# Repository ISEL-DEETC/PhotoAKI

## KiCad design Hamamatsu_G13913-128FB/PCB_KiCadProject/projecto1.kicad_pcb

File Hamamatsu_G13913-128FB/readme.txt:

This folder contains all the project files related to the multichannel optical detector
based on Hamamatsu's G13913-128FB linear image sensor.

Folder STM32_ImageSensor contains the Arduino project files for the STM32 microcontroller. 
Instructions on how to install the required packages and drivers to use STM32 MCU with
tne Arduino IDE are included in the main project file.

Folder PCB_KiCadProject contains the project files for the PCB in which the image sensor 
is mounted and connected to the MCU development board. The gerber files used to
manufacture the first prototype through JLCPCB's services are also included.

Folder ArduinoDue_TestSignals contains the Arduino project file for an ArduinoDue board
to generate test signals for the detection system.

Folder PhotonicImagingApp_Installer contains the installation files for the Windows
Application to control the detection module. The source files for the application
are archived in the VisualStudio_PhotonicImagingAppProject.zip file.

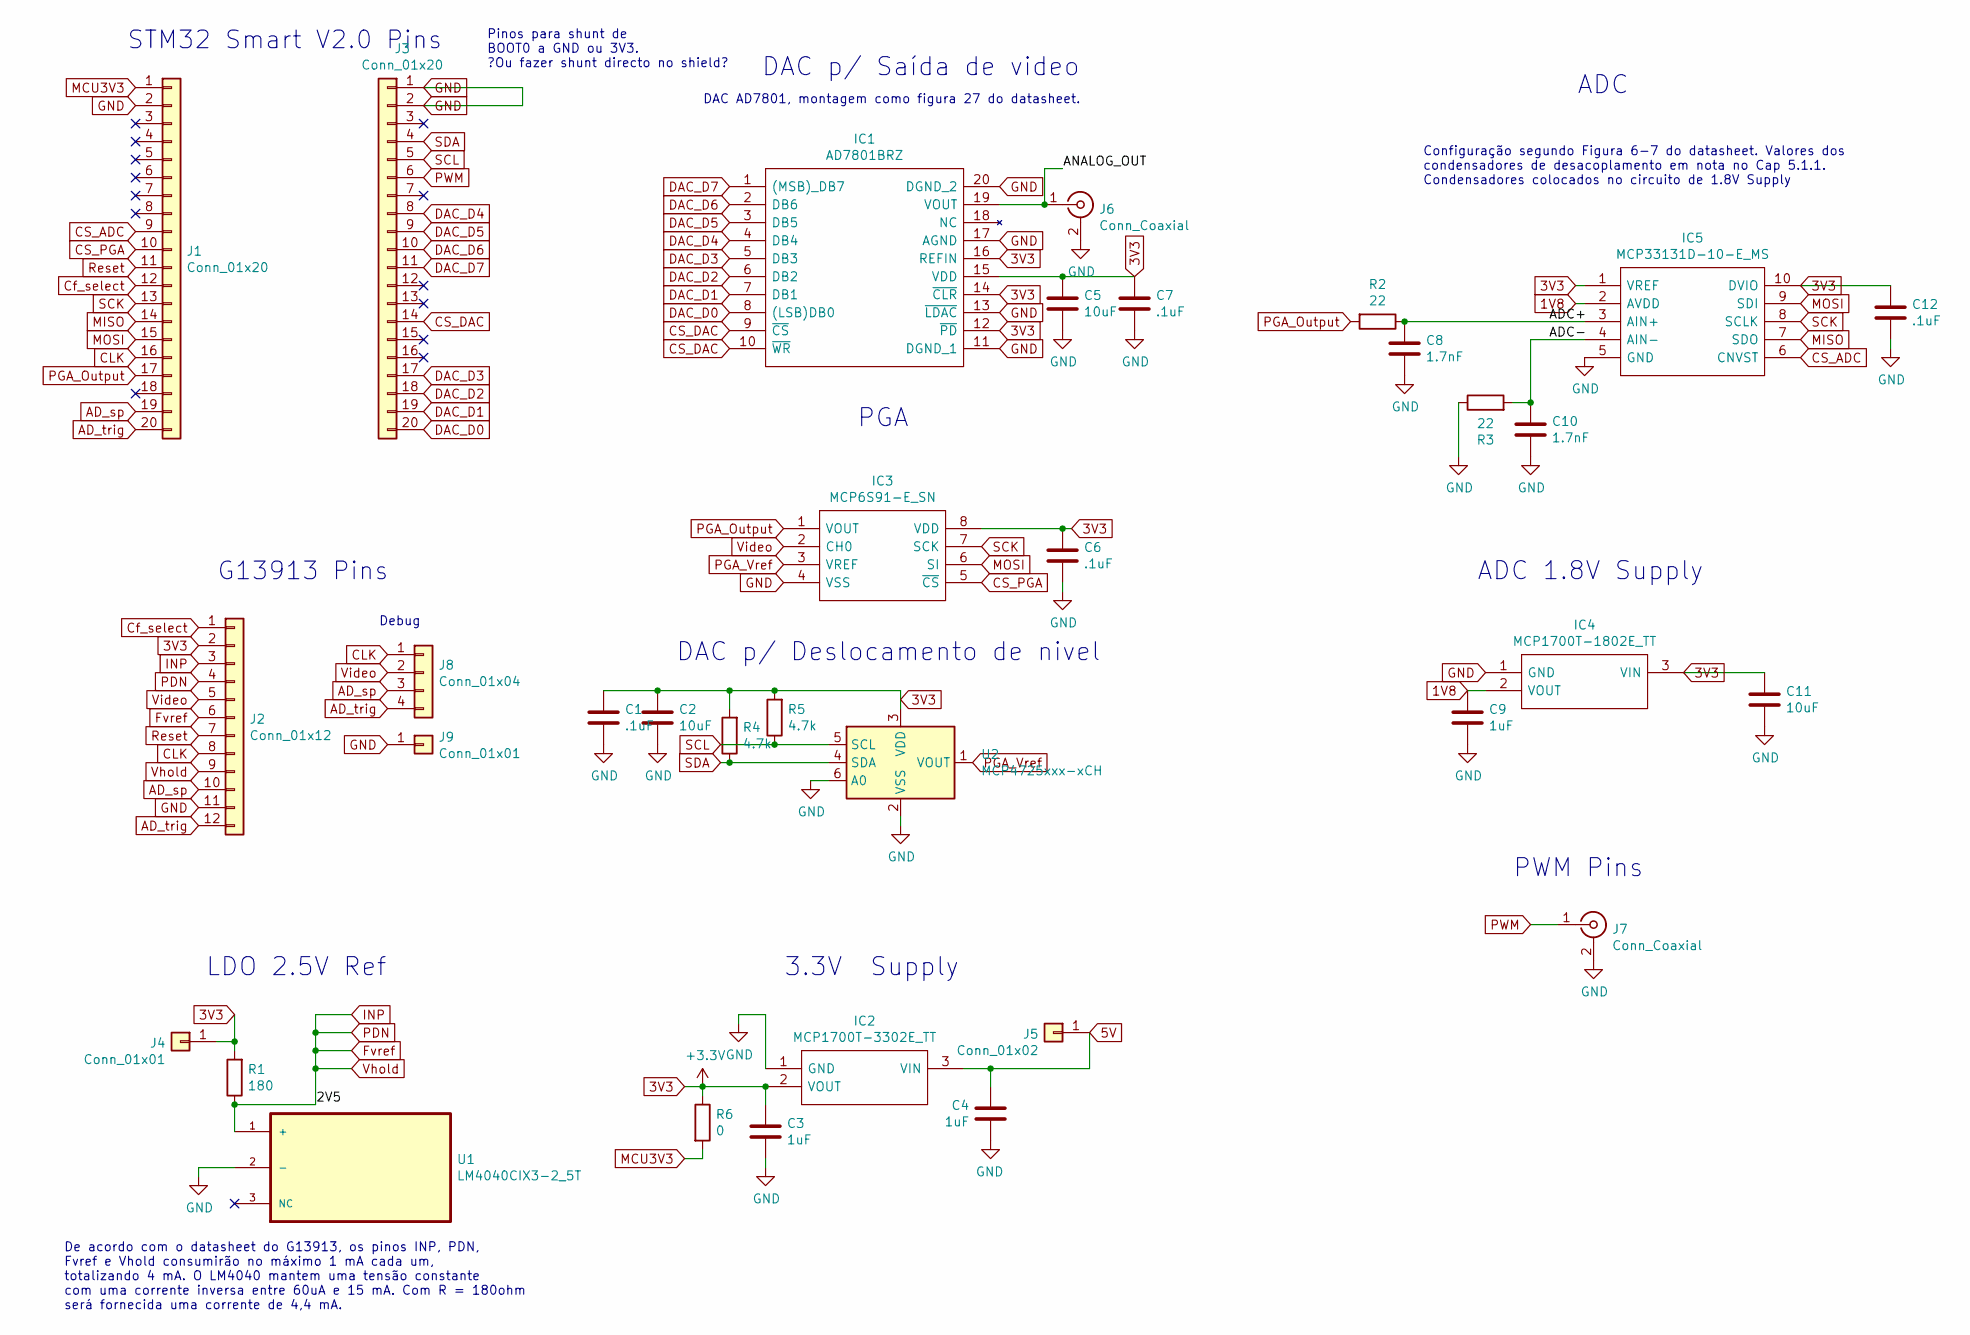
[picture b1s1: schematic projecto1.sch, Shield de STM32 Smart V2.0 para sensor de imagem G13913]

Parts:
C1, C6, C7, C12: .1uF; C_1206_3216Metric_Pad1.33x1.80mm_HandSolder
C2, C5, C11: 10uF; C_1206_3216Metric_Pad1.33x1.80mm_HandSolder
C3, C4, C9: 1uF; C_1206_3216Metric_Pad1.33x1.80mm_HandSolder
C8, C10: 1.7nF; C_1206_3216Metric_Pad1.33x1.80mm_HandSolder
IC1: AD7801BRZ; SOIC127P1032X265-20N; Manufacturer_Part_Number AD7801BRZ; Mouser Part Number 584-AD7801BRZ
IC2: MCP1700T-3302E_TT; SOT95P237X112-3N; Mouser Part Number 579-MCP1700T3302E/TT
IC3: MCP6S91-E_SN; SOIC127P600X175-8N; Manufacturer_Part_Number MCP6S91-E/SN; Mouser Part Number 579-MCP6S91-E/SN
IC4: MCP1700T-1802E_TT; SOT95P237X112-3N; Manufacturer_Part_Number MCP1700T-1802E/TT; Mouser Part Number 579-MCP1700T1802E/TT
IC5: MCP33131D-10-E_MS; SOP50P490X110-10N; Mouser Part Number 579-MCP33131D10EMS
J1, J3: Conn_01x20; PinHeader_1x20_P2.54mm_Vertical
J2: Conn_01x12; Hirose_FH12-12S-0.5SH_1x12-1MP_P0.50mm_Horizontal
J4, J9: Conn_01x01; PinHeader_1x01_P2.54mm_Vertical
J5: Conn_01x02; PinHeader_1x01_P2.54mm_Vertical
J6, J7: Conn_Coaxial; PCBSMAFRAHT
J8: Conn_01x04; PinHeader_1x04_P2.54mm_Vertical
R1: 180; R_1206_3216Metric_Pad1.30x1.75mm_HandSolder
R2, R3: 22; R_1206_3216Metric_Pad1.30x1.75mm_HandSolder
R4, R5: 4.7k; R_1206_3216Metric_Pad1.30x1.75mm_HandSolder
R6: 0; R_0805_2012Metric_Pad1.20x1.40mm_HandSolder
U1: LM4040CIX3-2_5T; SOT65P210X110-3N
U2: MCP4725xxx-xCH; SOT-23-6

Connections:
1V8: C9.1, IC4.2 (VOUT), IC5.2 (AVDD)
3V3: C1.1, C2.1, C3.1, C5.1, C6.1, C7.1, C11.1, C12.1, IC1.12 (~PD), IC1.14 (~CLR), IC1.15 (VDD), IC1.16 (REFIN), IC2.2 (VOUT), IC3.8 (VDD), IC4.3 (VIN), IC5.1 (VREF), IC5.10 (DVIO), J2.2, J4.1, R1.2, R4.2, R5.2, R6.1, U2.3 (VDD)
5V: C4.1, IC2.3 (VIN), J5.1
/ADC+: C8.1, IC5.3 (AIN+), R2.1
/ADC-: C10.1, IC5.4 (AIN-), R3.2
/ANALOG_OUT: IC1.19 (VOUT), J6.1 (In)
AD_sp: J1.19, J2.10, J8.3
AD_trig: J1.20, J2.12, J8.4
CLK: J1.16, J2.8, J8.1
CS_ADC: IC5.6 (CNVST), J1.9
CS_DAC: IC1.9 (~CS), IC1.10 (~WR), J3.14
CS_PGA: IC3.5 (~CS), J1.10
Cf_select: J1.12, J2.1
DAC_D0: IC1.8 ((LSB)DB0), J3.20
DAC_D1: IC1.7 (DB1), J3.19
DAC_D2: IC1.6 (DB2), J3.18
DAC_D3: IC1.5 (DB3), J3.17
DAC_D4: IC1.4 (DB4), J3.8
DAC_D5: IC1.3 (DB5), J3.9
DAC_D6: IC1.2 (DB6), J3.10
DAC_D7: IC1.1 ((MSB)_DB7), J3.11
Fvref: J2.3, J2.4, J2.6, J2.9, R1.1, U1.1 (+)
GND: C1.2, C2.2, C3.2, C4.2, C5.2, C6.2, C7.2, C8.2, C9.2, C10.2, C11.2, C12.2, IC1.11 (DGND_1), IC1.13 (~LDAC), IC1.17 (AGND), IC1.20 (DGND_2), IC2.1 (GND), IC3.4 (VSS), IC4.1 (GND), IC5.5 (GND), J1.2, J2.11, J3.1, J3.2, J6.2 (Ext), J6.4, J7.2 (Ext), J7.4, J9.1, R3.1, U1.2 (-), U2.2 (VSS), U2.6 (A0)
MCU3V3: J1.1, R6.2
MISO: IC5.7 (SDO), J1.14
MOSI: IC3.6 (SI), IC5.9 (SDI), J1.15
PGA_Output: IC3.1 (VOUT), J1.17, R2.2
PGA_Vref: IC3.3 (VREF), U2.1 (VOUT)
PWM: J3.6, J7.1 (In)
Reset: J1.11, J2.7
SCK: IC3.7 (SCK), IC5.8 (SCLK), J1.13
SCL: J3.5, R5.1, U2.5 (SCL)
SDA: J3.4, R4.1, U2.4 (SDA)
Video: IC3.2 (CH0), J2.5, J8.2

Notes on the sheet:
STM32 Smart V2.0 Pins
G13913 Pins
ADC 1.8V Supply
LDO 2.5V Ref
3.3V Supply
DAC p/ Saída de video
ADC
PGA
Configuração segundo Figura 6-7 do datasheet. Valores dos condensadores de desacoplamento em nota no Cap 5.1.1. Condensadores colocados no circuito de 1.8V Supply
DAC AD7801, montagem como figura 27 do datasheet.
Pinos para shunt de BOOT0 a GND ou 3V3. ?Ou fazer shunt directo no shield?
DAC p/ Deslocamento de nivel
PWM Pins
De acordo com o datasheet do G13913, os pinos INP, PDN, Fvref e Vhold consumirão no máximo 1 mA cada um, totalizando 4 mA. O LM4040 mantem uma tensão constante com uma corrente inversa entre 60uA e 15 mA. Com R = 180ohm será fornecida uma corrente de 4,4 mA.
Debug

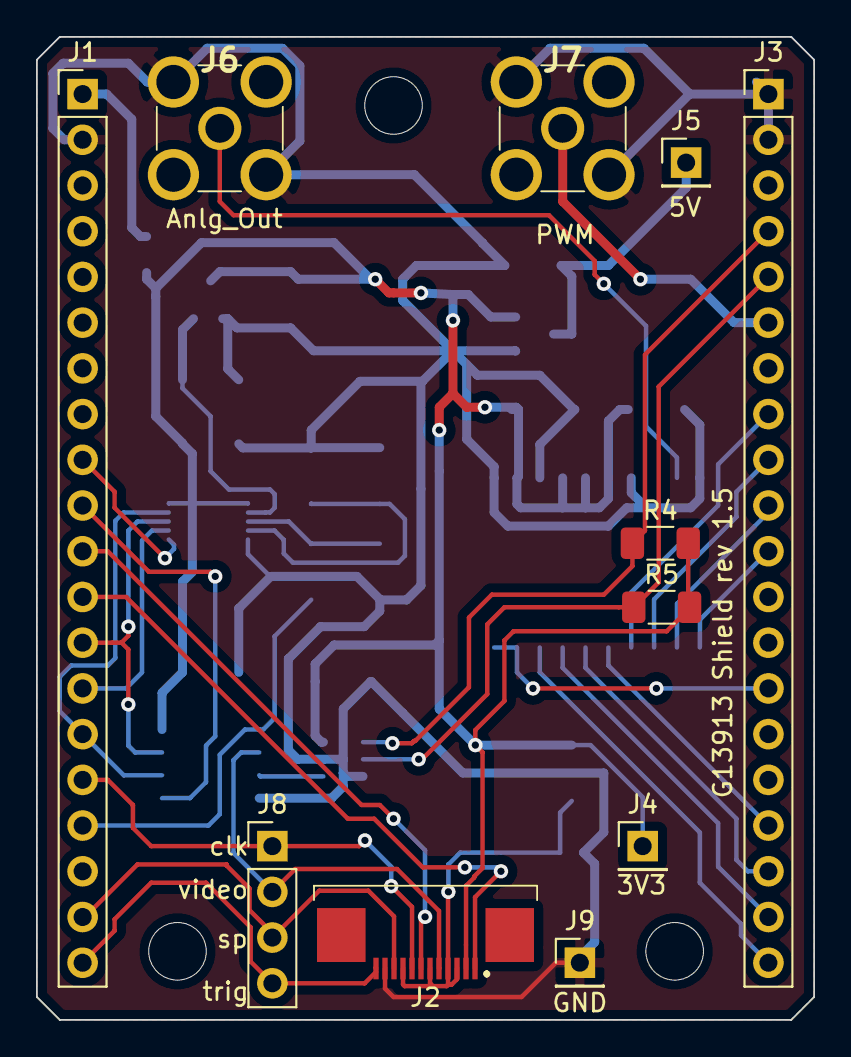
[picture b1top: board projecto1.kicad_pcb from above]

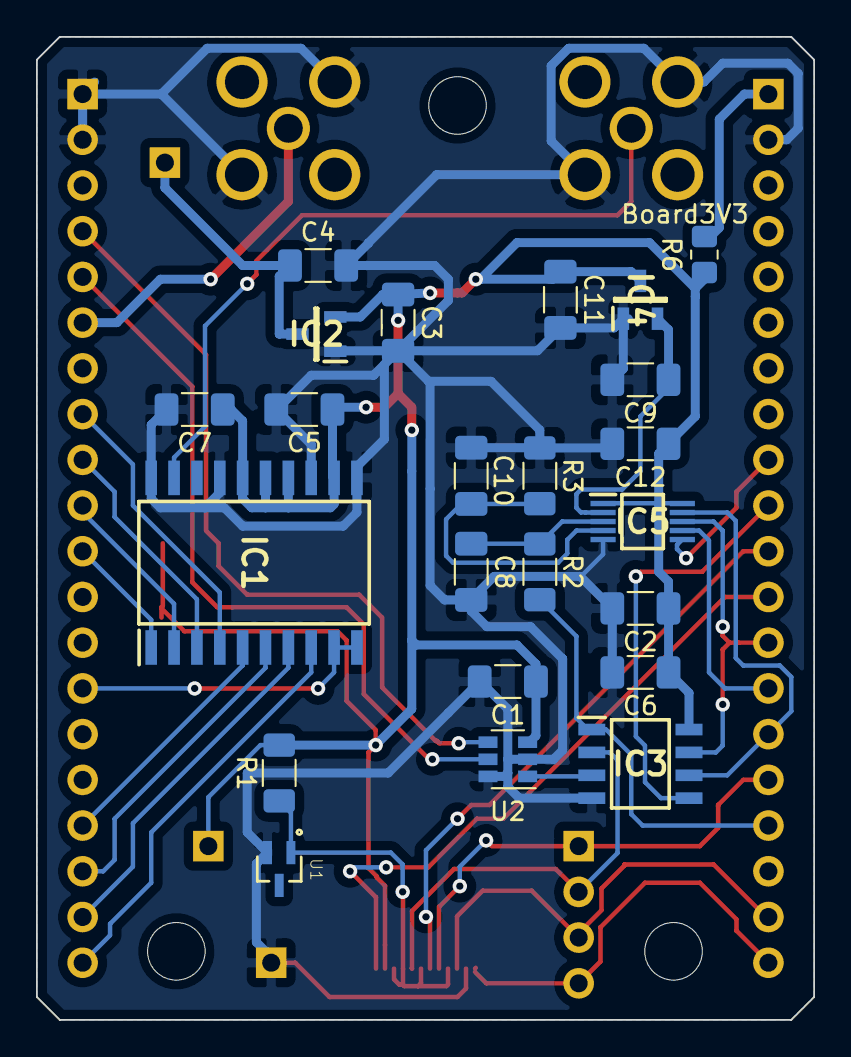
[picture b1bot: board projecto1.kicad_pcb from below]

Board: 2 copper layers, 43.2 x 54.6 mm, 34 parts (23 on the bottom side), 34 nets.

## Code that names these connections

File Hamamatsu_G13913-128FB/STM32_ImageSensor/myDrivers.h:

#ifndef _MYDRIVERS_H_
#define _MYDRIVERS_H_

#define HAL_EXTI_MODULE_ENABLED

#include <Arduino.h>
#include "SPI.h"

#define PIN_MOSI       PA7
#define PIN_MISO       PA6
#define PIN_SCK        PA5
#define PIN_CSEL       PA4
#define PIN_CLOCK      PB0
#define PIN_ADC_IN     PB1
#define PIN_ADC_START  PB10
#define PIN_ADC_TRIG   PB11
#define PIN_RESET      PA3
#define PIN_PWM        PB7  
#define PIN_CS_DAC     PA10
#define PIN_CS_PGA     PA2
#define PIN_CS_ADC     PA1

#define PIN_DAC_0      PB12
#define PIN_DAC_1      PB13
#define PIN_DAC_2      PB14
#define PIN_DAC_3      PB15
#define PIN_DAC_4      PB5
#define PIN_DAC_5      PB4
#define PIN_DAC_6      PB3
#define PIN_DAC_7      PA15

#define ADC_MAX_VAL       4095
#define EXT_ADC_MAX_VAL  32767    // 15 bits are used in single-ended mode of operation
#define ADC_REF_MILIVOLT  3300

extern volatile uint16_t data[128];

/* Clock pin functions */

void Clock_Setup(float freq);
void Clock_Start();
void Clock_Stop();
void Clock_Freq(float freq);

/* Reset pin functions */
void Reset_Setup();
void Reset_Pulse_us(uint32_t us);

/* Cf Sel pin functions */
void CfSel_Setup();
void CfSel_On();
void CfSel_Off();

/* PWM pin functions */
void PWM_Setup();
void PWM_Config(uint32_t period_us, float dutyCycle);
void PWM_Start();
void PWM_Stop();

/* Internal and external ADC functions */
void ADC_Setup();
void ADC_Prepare();
int ADC_WaitSequence(uint32_t timeout);
void ADC_GetData(uint16_t newData[128]);
void ExternalADC_Setup();
void ExternalADC_Calibrate();
void ExternalADC_Enable();
void ExternalADC_Disable();
int16_t ADC_SingleConvertion();

void SetSPIFreq(uint32_t freq);

/* Conditioning circuit functions  */
void PGA_Setup();
void PGA_SetGain(const uint8_t g);
void Vref_Setup();
bool Vref_Set(uint32_t val);
bool Vref_TestDevice();

/* Analog output functions */ 
void AnalogOut_Setup(uint32_t freq);
void AnalogOut_SetFreq(uint32_t freq);
void AnalogOut_WriteWord(uint8_t value);
void AnalogOut_WriteArray(uint8_t *data, uint32_t n);

#endif

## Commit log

2022-12-22 Add files via upload
    The system allows the fine tuning of an optical fiber position on an input grating, controlling its XYZ position and its angle of incidence. A similar configuration is used for the output extraction,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
